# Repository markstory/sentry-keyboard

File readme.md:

# sentry-keyboard

A reverse engineered PCB for the keyboard that Sentry gave as holiday gift in 2024.

## Features

- Per key RGB LEDs
- Rotary encoder with switch
- USB host interface connection through picoblade connector.
- Programmable keymap with QMK

## Building the Firmware

The `firmware` directory of this repostiory contains only the files specific
to this keyboards firmware, and does not include all of QMK. To build firmware you
need to have a copy of QMK (lets assume it is at `~/code/qmk)`:

```bash
cp -R firmware/* ~/code/qmk/keyboards/sentry-keyboard
cd ~/code/qmk
qmk compile -kb sentry-keyboard -km default
```

This will compile a `.hex` file that you can flash onto your keyboard

```bash
qmk flash -kb sentry-keyboard
```

Brand new micro controller chips may have not have the bootloader initialized, 
and you'll need to erase the chip first:

```bash
dfu-programmer atmega32u4 erase
```

Once the chip has been erased you can flash the firmware on.

## License

Both the PCB design and firmware are provided under the MIT License

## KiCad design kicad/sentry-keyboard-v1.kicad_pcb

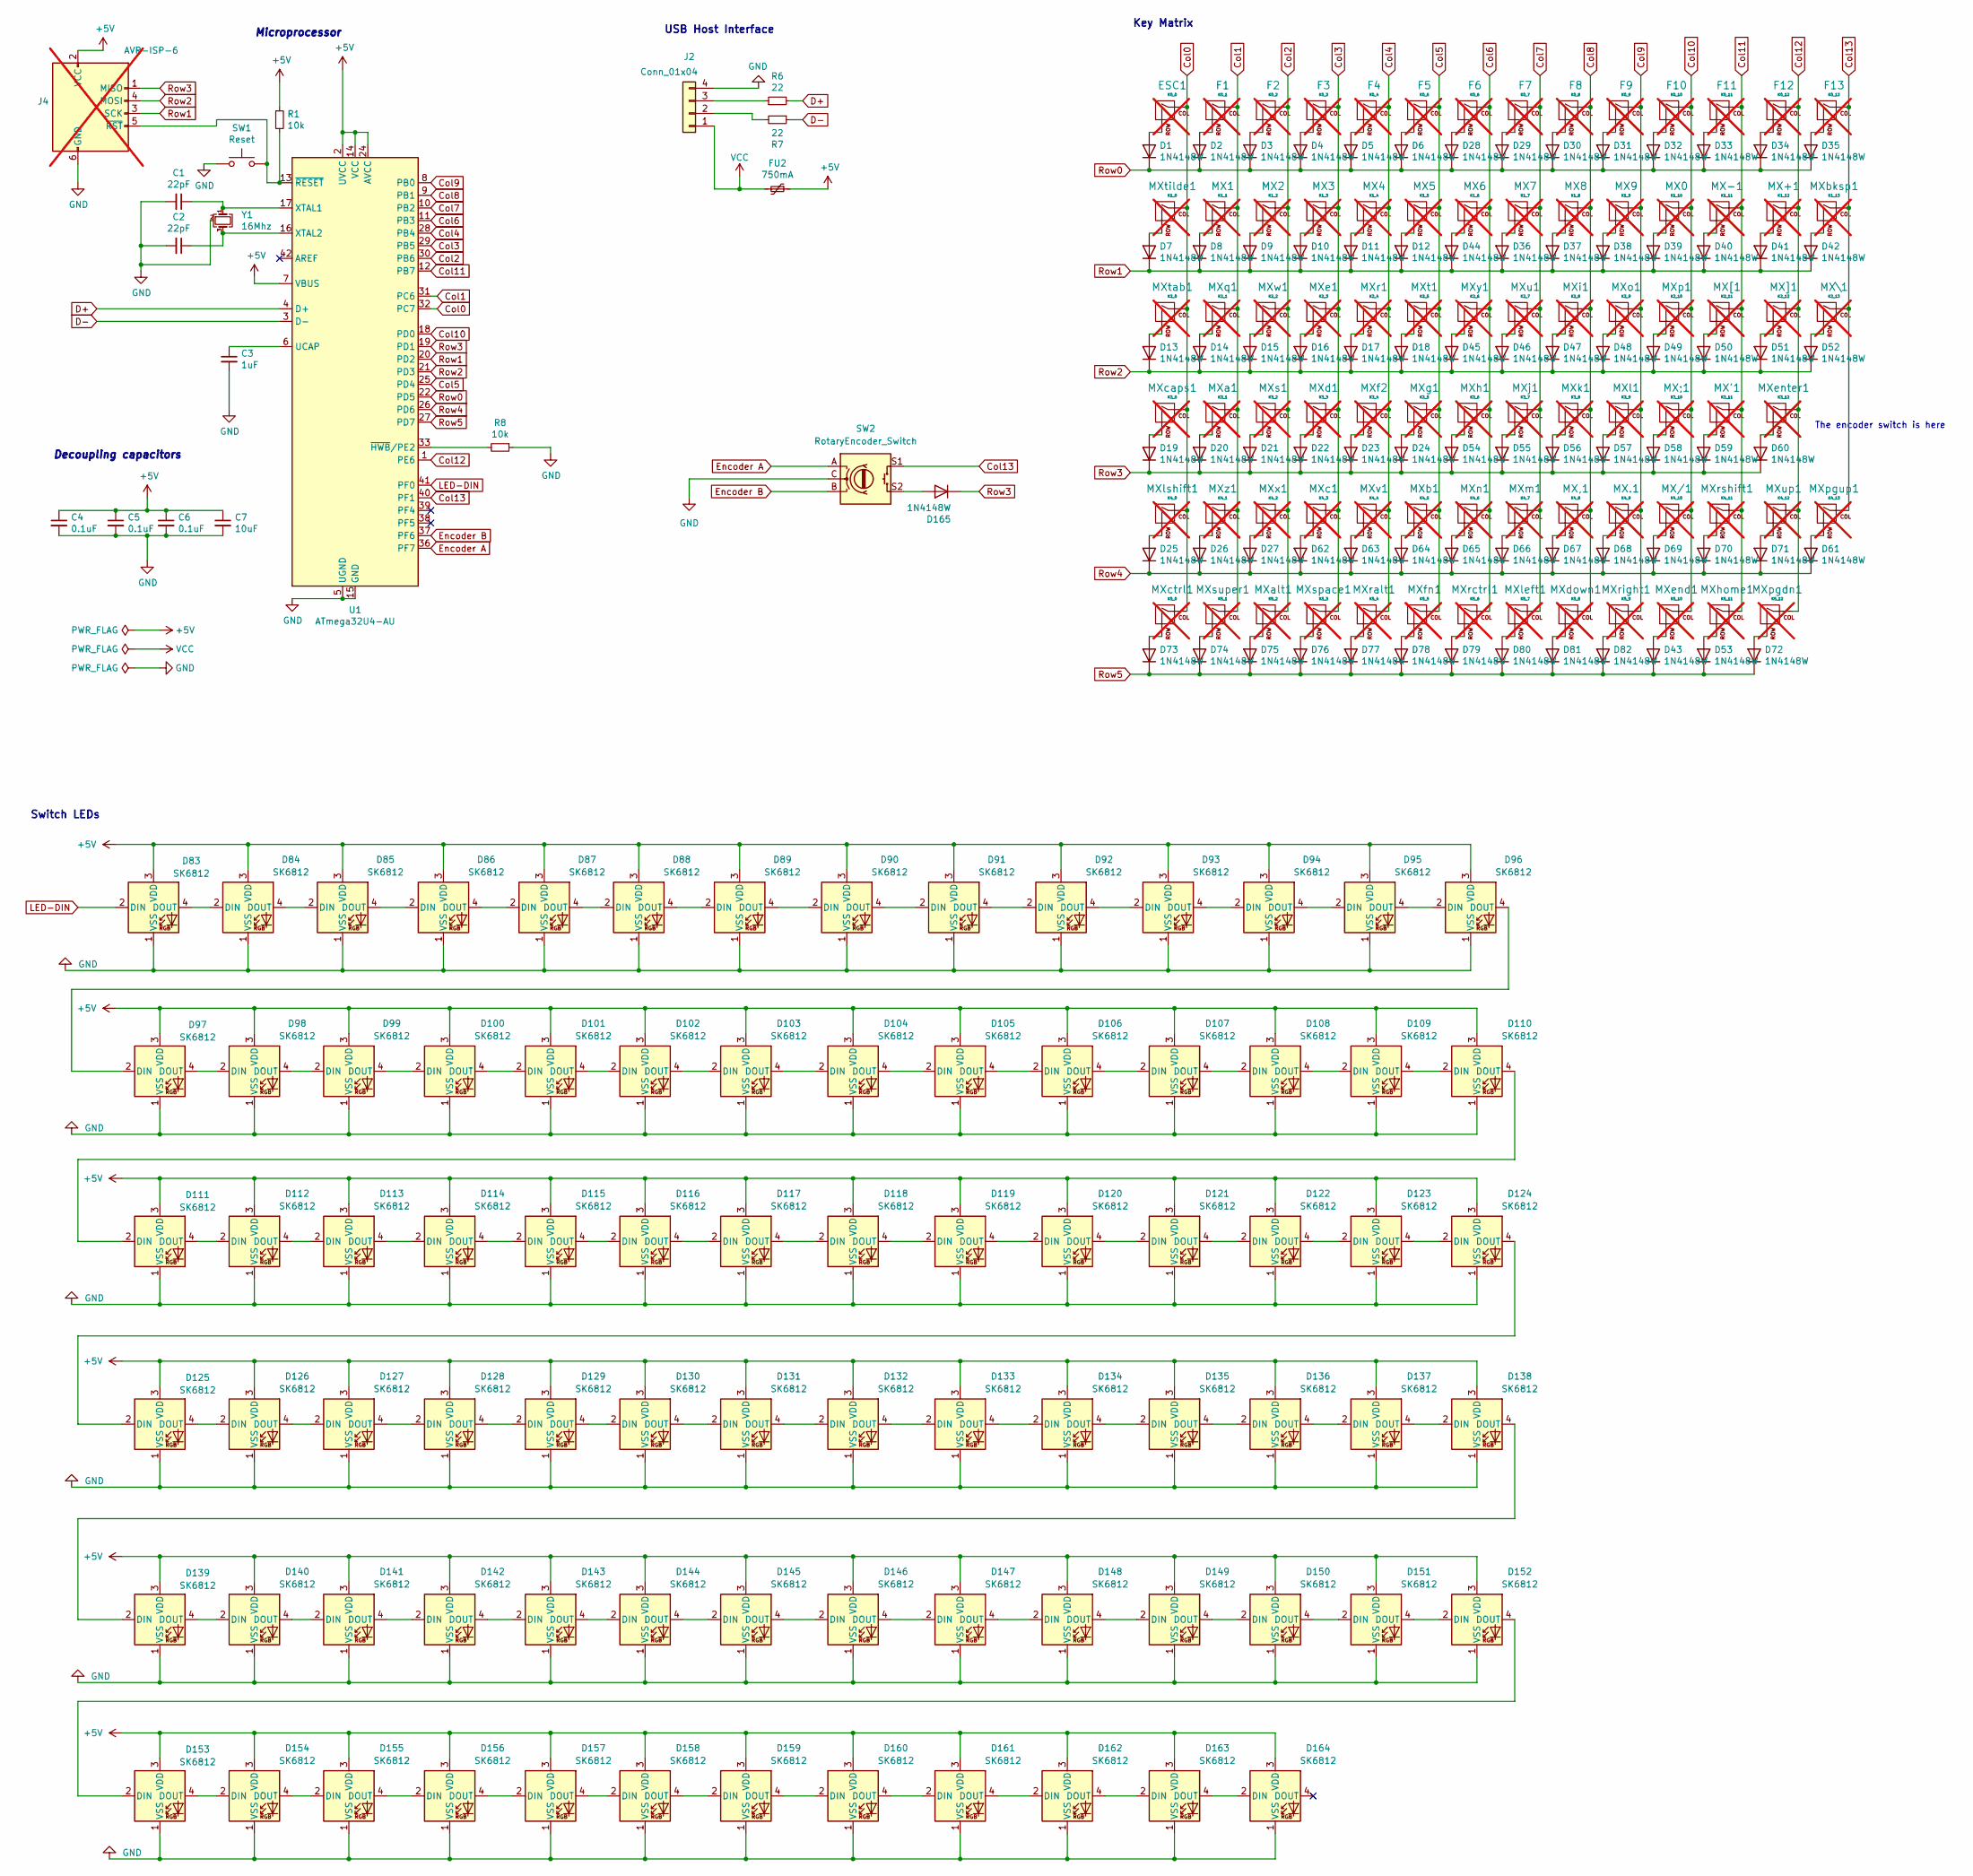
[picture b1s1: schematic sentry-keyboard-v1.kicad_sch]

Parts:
C1, C2: 22pF; C_0805_2012Metric; LCSC Part # C105623
C3: 1uF; C_0805_2012Metric; LCSC Part # C472813
C4, C5, C6: 0.1uF; C_0805_2012Metric; LCSC Part # C49678
C7: 10uF; C_0805_2012Metric; LCSC Part # C307520
D1, D2, D3, D4, D5, D6, D7, D8, D9, D10, D11, D12, D13, D14, D15, D16, D17, D18, D19, D20, D21, D22, D23, D24, D25, D26, D27, D28, D29, D30, D31, D32, D33, D34, D35, D36, D37, D38, D39, D40, D41, D42, D43, D44, D45, D46, D47, D48, D49, D50, D51, D52, D53, D54, D55, D56, D57, D58, D59, D60, D61, D62, D63, D64, D65, D66, D67, D68, D69, D70, D71, D72, D73, D74, D75, D76, D77, D78, D79, D80, D81, D82, D165: 1N4148W; D_SOD-123; LCSC Part # C7420318
D83, D84, D85, D86, D87, D88, D89, D90, D91, D92, D93, D94, D95, D96, D97, D98, D99, D100, D101, D102, D103, D104, D105, D106, D107, D108, D109, D110, D111, D112, D113, D114, D115, D116, D117, D118, D119, D120, D121, D122, D123, D124, D125, D126, D127, D128, D129, D130, D131, D132, D133, D134, D135, D136, D137, D138, D139, D140, D141, D142, D143, D144, D145, D146, D147, D148, D149, D150, D151, D152, D153, D154, D155, D156, D157, D158, D159, D160, D161, D162, D163, D164: SK6812; SK6812-MINI-E; LCSC Part # C5149201
ESC1: K0_0; MX-Hotswap-1U; not fitted
F1: K0_1; MX-Hotswap-1U; not fitted
F2: K0_2; MX-Hotswap-1U; not fitted
F3: K0_3; MX-Hotswap-1U; not fitted
F4: K0_4; MX-Hotswap-1U; not fitted
F5: K0_5; MX-Hotswap-1U; not fitted
F6: K0_6; MX-Hotswap-1U; not fitted
F7: K0_7; MX-Hotswap-1U; not fitted
F8: K0_8; MX-Hotswap-1U; not fitted
F9: K0_9; MX-Hotswap-1U; not fitted
F10: K0_10; MX-Hotswap-1U; not fitted
F11: K0_11; MX-Hotswap-1U; not fitted
F12: K0_12; MX-Hotswap-1U; not fitted
F13: K0_13; MX-Hotswap-1U; not fitted
FU2: 750mA; Fuse_1206_3216Metric_Pad1.42x1.75mm_HandSolder; LCSC Part # C46641018
J2: Conn_01x04; Molex_PicoBlade_53261-0471_1x04-1MP_P1.25mm_Horizontal; LCSC Part # C696092
J4: AVR-ISP-6; Reset_Pretty-Mask; not fitted
MX0: K1_10; MX-Hotswap-1U; not fitted
MX1: K1_1; MX-Hotswap-1U; not fitted
MX2: K1_2; MX-Hotswap-1U; not fitted
MX3: K1_3; MX-Hotswap-1U; not fitted
MX4: K1_4; MX-Hotswap-1U; not fitted
MX5: K1_5; MX-Hotswap-1U; not fitted
MX6: K1_6; MX-Hotswap-1U; not fitted
MX7: K1_7; MX-Hotswap-1U; not fitted
MX8: K1_8; MX-Hotswap-1U; not fitted
MX9: K1_9; MX-Hotswap-1U; not fitted
MX'1: K3_11; MX-Hotswap-1U; not fitted
MX+1: K1_12; MX-Hotswap-1U; not fitted
MX,1: K4_8; MX-Hotswap-1U; not fitted
MX-1: K1_11; MX-Hotswap-1U; not fitted
MX.1: K4_9; MX-Hotswap-1U; not fitted
MX/1: K4_10; MX-Hotswap-1U; not fitted
MX;1: K3_10; MX-Hotswap-1U; not fitted
MX[1: K2_11; MX-Hotswap-1U; not fitted
MX\1: K2_13; MX-Hotswap-1.5U; not fitted
MX]1: K2_12; MX-Hotswap-1U; not fitted
MXa1: K3_1; MX-Hotswap-1U; not fitted
MXalt1: K5_2; MX-Hotswap-1.25U; not fitted
MXb1: K4_5; MX-Hotswap-1U; not fitted
MXbksp1: K1_13; MX-Hotswap-2U; not fitted
MXc1: K4_3; MX-Hotswap-1U; not fitted
MXcaps1: K3_0; MX-Hotswap-1.75U; not fitted
MXctrl1: K5_0; MX-Hotswap-1.25U; not fitted
MXd1: K3_3; MX-Hotswap-1U; not fitted
MXdown1: K5_8; MX-Hotswap-1U; not fitted
MXe1: K2_3; MX-Hotswap-1U; not fitted
MXend1: K5_10; MX-Hotswap-1U; not fitted
MXenter1: K3_12; MX-Hotswap-2.25U-ReversedStabilizers; not fitted
MXf2: K3_4; MX-Hotswap-1U; not fitted
MXfn1: K5_5; MX-Hotswap-1U; not fitted
MXg1: K3_5; MX-Hotswap-1U; not fitted
MXh1: K3_6; MX-Hotswap-1U; not fitted
MXhome1: K5_11; MX-Hotswap-1U; not fitted
MXi1: K2_8; MX-Hotswap-1U; not fitted
MXj1: K3_7; MX-Hotswap-1U; not fitted
MXk1: K3_8; MX-Hotswap-1U; not fitted
MXl1: K3_9; MX-Hotswap-1U; not fitted
MXleft1: K5_7; MX-Hotswap-1U; not fitted
MXlshift1: K4_0; MX-Hotswap-2.25U; not fitted
MXm1: K4_7; MX-Hotswap-1U; not fitted
MXn1: K4_6; MX-Hotswap-1U; not fitted
MXo1: K2_9; MX-Hotswap-1U; not fitted
MXp1: K2_10; MX-Hotswap-1U; not fitted
MXpgdn1: K5_12; MX-Hotswap-1U; not fitted
MXpgup1: K4_13; MX-Hotswap-1U; not fitted
MXq1: K2_1; MX-Hotswap-1U; not fitted
MXr1: K2_4; MX-Hotswap-1U; not fitted
MXralt1: K5_4; MX-Hotswap-1U; not fitted
MXrctrl1: K5_6; MX-Hotswap-1U; not fitted
MXright1: K5_9; MX-Hotswap-1U; not fitted
MXrshift1: K4_11; MX-Hotswap-1.75U; not fitted
MXs1: K3_2; MX-Hotswap-1U; not fitted
MXspace1: K5_3; MX-Hotswap-6.25U-ReversedStabilizers; not fitted
MXsuper1: K5_1; MX-Hotswap-1.25U; not fitted
MXt1: K2_5; MX-Hotswap-1U; not fitted
MXtab1: K2_0; MX-Hotswap-1.5U; not fitted
MXtilde1: K1_0; MX-Hotswap-1U; not fitted
MXu1: K2_7; MX-Hotswap-1U; not fitted
MXup1: K4_12; MX-Hotswap-1U; not fitted
MXv1: K4_4; MX-Hotswap-1U; not fitted
MXw1: K2_2; MX-Hotswap-1U; not fitted
MXx1: K4_2; MX-Hotswap-1U; not fitted
MXy1: K2_6; MX-Hotswap-1U; not fitted
MXz1: K4_1; MX-Hotswap-1U; not fitted
R1, R8: 10k; R_0805_2012Metric; LCSC Part # C180849
R6, R7: 22; R_0805_2012Metric; LCSC Part # C413152
SW1: Reset; SW_SPST_TL3342; LCSC Part # C720467
SW2: RotaryEncoder_Switch; RotaryEncoder_EC11; LCSC Part # C470748
U1: ATmega32U4-AU; TQFP-44_10x10mm_P0.8mm; LCSC Part # C44854
Y1: 16Mhz; Crystal_SMD_3225-4Pin_3.2x2.5mm; LCSC Part # C258944

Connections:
+5V: C4.1, C5.1, C6.1, C7.1, D83.3 (VDD), D84.3 (VDD), D85.3 (VDD), D86.3 (VDD), D87.3 (VDD), D88.3 (VDD), D89.3 (VDD), D90.3 (VDD), D91.3 (VDD), D92.3 (VDD), D93.3 (VDD), D94.3 (VDD), D95.3 (VDD), D96.3 (VDD), D97.3 (VDD), D98.3 (VDD), D99.3 (VDD), D100.3 (VDD), D101.3 (VDD), D102.3 (VDD), D103.3 (VDD), D104.3 (VDD), D105.3 (VDD), D106.3 (VDD), D107.3 (VDD), D108.3 (VDD), D109.3 (VDD), D110.3 (VDD), D111.3 (VDD), D112.3 (VDD), D113.3 (VDD), D114.3 (VDD), D115.3 (VDD), D116.3 (VDD), D117.3 (VDD), D118.3 (VDD), D119.3 (VDD), D120.3 (VDD), D121.3 (VDD), D122.3 (VDD), D123.3 (VDD), D124.3 (VDD), D125.3 (VDD), D126.3 (VDD), D127.3 (VDD), D128.3 (VDD), D129.3 (VDD), D130.3 (VDD), D131.3 (VDD), D132.3 (VDD), D133.3 (VDD), D134.3 (VDD), D135.3 (VDD), D136.3 (VDD), D137.3 (VDD), D138.3 (VDD), D139.3 (VDD), D140.3 (VDD), D141.3 (VDD), D142.3 (VDD), D143.3 (VDD), D144.3 (VDD), D145.3 (VDD), D146.3 (VDD), D147.3 (VDD), D148.3 (VDD), D149.3 (VDD), D150.3 (VDD), D151.3 (VDD), D152.3 (VDD), D153.3 (VDD), D154.3 (VDD), D155.3 (VDD), D156.3 (VDD), D157.3 (VDD), D158.3 (VDD), D159.3 (VDD), D160.3 (VDD), D161.3 (VDD), D162.3 (VDD), D163.3 (VDD), D164.3 (VDD), FU2.1, J4.2 (VCC), R1.1, U1.2 (UVCC), U1.7 (VBUS), U1.14 (VCC), U1.24 (AVCC), U1.34 (VCC), U1.44 (AVCC)
Col0: ESC1.1 (COL), MXcaps1.1 (COL), MXctrl1.1 (COL), MXlshift1.1 (COL), MXtab1.1 (COL), MXtilde1.1 (COL), U1.32 (PC7)
Col1: F1.1 (COL), MX1.1 (COL), MXa1.1 (COL), MXq1.1 (COL), MXsuper1.1 (COL), MXz1.1 (COL), U1.31 (PC6)
Col2: F2.1 (COL), MX2.1 (COL), MXalt1.1 (COL), MXs1.1 (COL), MXw1.1 (COL), MXx1.1 (COL), U1.30 (PB6)
Col3: F3.1 (COL), MX3.1 (COL), MXc1.1 (COL), MXd1.1 (COL), MXe1.1 (COL), MXspace1.1 (COL), U1.29 (PB5)
Col4: F4.1 (COL), MX4.1 (COL), MXf2.1 (COL), MXr1.1 (COL), MXralt1.1 (COL), MXv1.1 (COL), U1.28 (PB4)
Col5: F5.1 (COL), MX5.1 (COL), MXb1.1 (COL), MXfn1.1 (COL), MXg1.1 (COL), MXt1.1 (COL), U1.25 (PD4)
Col6: F6.1 (COL), MX6.1 (COL), MXh1.1 (COL), MXn1.1 (COL), MXrctrl1.1 (COL), MXy1.1 (COL), U1.11 (PB3)
Col7: F7.1 (COL), MX7.1 (COL), MXj1.1 (COL), MXleft1.1 (COL), MXm1.1 (COL), MXu1.1 (COL), U1.10 (PB2)
Col8: F8.1 (COL), MX8.1 (COL), MX,1.1 (COL), MXdown1.1 (COL), MXi1.1 (COL), MXk1.1 (COL), U1.9 (PB1)
Col9: F9.1 (COL), MX9.1 (COL), MX.1.1 (COL), MXl1.1 (COL), MXo1.1 (COL), MXright1.1 (COL), U1.8 (PB0)
Col10: F10.1 (COL), MX0.1 (COL), MX/1.1 (COL), MX;1.1 (COL), MXend1.1 (COL), MXp1.1 (COL), U1.18 (PD0)
Col11: F11.1 (COL), MX'1.1 (COL), MX-1.1 (COL), MX[1.1 (COL), MXhome1.1 (COL), MXrshift1.1 (COL), U1.12 (PB7)
Col12: F12.1 (COL), MX+1.1 (COL), MX]1.1 (COL), MXenter1.1 (COL), MXpgdn1.1 (COL), MXup1.1 (COL), U1.1 (PE6)
Col13: F13.1 (COL), MX\1.1 (COL), MXbksp1.1 (COL), MXpgup1.1 (COL), SW2.S1, U1.40 (PF1)
D+: R6.2, U1.4 (D+)
D-: R7.1, U1.3 (D-)
Encoder A: SW2.A, U1.36 (PF7)
Encoder B: SW2.B, U1.37 (PF6)
GND: C1.2, C2.2, C3.2, C4.2, C5.2, C6.2, C7.2, D83.1 (VSS), D84.1 (VSS), D85.1 (VSS), D86.1 (VSS), D87.1 (VSS), D88.1 (VSS), D89.1 (VSS), D90.1 (VSS), D91.1 (VSS), D92.1 (VSS), D93.1 (VSS), D94.1 (VSS), D95.1 (VSS), D96.1 (VSS), D97.1 (VSS), D98.1 (VSS), D99.1 (VSS), D100.1 (VSS), D101.1 (VSS), D102.1 (VSS), D103.1 (VSS), D104.1 (VSS), D105.1 (VSS), D106.1 (VSS), D107.1 (VSS), D108.1 (VSS), D109.1 (VSS), D110.1 (VSS), D111.1 (VSS), D112.1 (VSS), D113.1 (VSS), D114.1 (VSS), D115.1 (VSS), D116.1 (VSS), D117.1 (VSS), D118.1 (VSS), D119.1 (VSS), D120.1 (VSS), D121.1 (VSS), D122.1 (VSS), D123.1 (VSS), D124.1 (VSS), D125.1 (VSS), D126.1 (VSS), D127.1 (VSS), D128.1 (VSS), D129.1 (VSS), D130.1 (VSS), D131.1 (VSS), D132.1 (VSS), D133.1 (VSS), D134.1 (VSS), D135.1 (VSS), D136.1 (VSS), D137.1 (VSS), D138.1 (VSS), D139.1 (VSS), D140.1 (VSS), D141.1 (VSS), D142.1 (VSS), D143.1 (VSS), D144.1 (VSS), D145.1 (VSS), D146.1 (VSS), D147.1 (VSS), D148.1 (VSS), D149.1 (VSS), D150.1 (VSS), D151.1 (VSS), D152.1 (VSS), D153.1 (VSS), D154.1 (VSS), D155.1 (VSS), D156.1 (VSS), D157.1 (VSS), D158.1 (VSS), D159.1 (VSS), D160.1 (VSS), D161.1 (VSS), D162.1 (VSS), D163.1 (VSS), D164.1 (VSS), J2.4, J4.6 (GND), R8.1, SW1.1, SW2.C, U1.5 (UGND), U1.15 (GND), U1.23 (GND), U1.35 (GND), U1.43 (GND), Y1.2 (G), Y1.4 (G)
LED-DIN: D83.2 (DIN), U1.41 (PF0)
unnamed: D1.2 (A), ESC1.2 (ROW)
unnamed: D2.2 (A), F1.2 (ROW)
unnamed: D3.2 (A), F2.2 (ROW)
unnamed: D4.2 (A), F3.2 (ROW)
unnamed: D5.2 (A), F4.2 (ROW)
unnamed: D6.2 (A), F5.2 (ROW)
unnamed: D7.2 (A), MXtilde1.2 (ROW)
unnamed: D8.2 (A), MX1.2 (ROW)
unnamed: D9.2 (A), MX2.2 (ROW)
unnamed: D10.2 (A), MX3.2 (ROW)
unnamed: D11.2 (A), MX4.2 (ROW)
unnamed: D12.2 (A), MX5.2 (ROW)
unnamed: D13.2 (A), MXtab1.2 (ROW)
unnamed: D14.2 (A), MXq1.2 (ROW)
unnamed: D15.2 (A), MXw1.2 (ROW)
unnamed: D16.2 (A), MXe1.2 (ROW)
unnamed: D17.2 (A), MXr1.2 (ROW)
unnamed: D18.2 (A), MXt1.2 (ROW)
unnamed: D19.2 (A), MXcaps1.2 (ROW)
unnamed: D20.2 (A), MXa1.2 (ROW)
unnamed: D21.2 (A), MXs1.2 (ROW)
unnamed: D22.2 (A), MXd1.2 (ROW)
unnamed: D23.2 (A), MXf2.2 (ROW)
unnamed: D24.2 (A), MXg1.2 (ROW)
unnamed: D25.2 (A), MXlshift1.2 (ROW)
unnamed: D26.2 (A), MXz1.2 (ROW)
unnamed: D27.2 (A), MXx1.2 (ROW)
unnamed: D28.2 (A), F6.2 (ROW)
unnamed: D29.2 (A), F7.2 (ROW)
unnamed: D30.2 (A), F8.2 (ROW)
unnamed: D31.2 (A), F9.2 (ROW)
unnamed: D32.2 (A), F10.2 (ROW)
unnamed: D33.2 (A), F11.2 (ROW)
unnamed: D34.2 (A), F12.2 (ROW)
unnamed: D35.2 (A), F13.2 (ROW)
unnamed: D36.2 (A), MX7.2 (ROW)
unnamed: D37.2 (A), MX8.2 (ROW)
unnamed: D38.2 (A), MX9.2 (ROW)
unnamed: D39.2 (A), MX0.2 (ROW)
unnamed: D40.2 (A), MX-1.2 (ROW)
unnamed: D41.2 (A), MX+1.2 (ROW)
unnamed: D42.2 (A), MXbksp1.2 (ROW)
unnamed: D43.2 (A), MXend1.2 (ROW)
unnamed: D44.2 (A), MX6.2 (ROW)
unnamed: D45.2 (A), MXy1.2 (ROW)
unnamed: D46.2 (A), MXu1.2 (ROW)
unnamed: D47.2 (A), MXi1.2 (ROW)
unnamed: D48.2 (A), MXo1.2 (ROW)
unnamed: D49.2 (A), MXp1.2 (ROW)
unnamed: D50.2 (A), MX[1.2 (ROW)
unnamed: D51.2 (A), MX]1.2 (ROW)
unnamed: D52.2 (A), MX\1.2 (ROW)
unnamed: D53.2 (A), MXhome1.2 (ROW)
unnamed: D54.2 (A), MXh1.2 (ROW)
unnamed: D55.2 (A), MXj1.2 (ROW)
unnamed: D56.2 (A), MXk1.2 (ROW)
unnamed: D57.2 (A), MXl1.2 (ROW)
unnamed: D58.2 (A), MX;1.2 (ROW)
unnamed: D59.2 (A), MX'1.2 (ROW)
unnamed: D60.2 (A), MXenter1.2 (ROW)
unnamed: D61.2 (A), MXpgup1.2 (ROW)
unnamed: D62.2 (A), MXc1.2 (ROW)
unnamed: D63.2 (A), MXv1.2 (ROW)
unnamed: D64.2 (A), MXb1.2 (ROW)
unnamed: D65.2 (A), MXn1.2 (ROW)
unnamed: D66.2 (A), MXm1.2 (ROW)
unnamed: D67.2 (A), MX,1.2 (ROW)
unnamed: D68.2 (A), MX.1.2 (ROW)
unnamed: D69.2 (A), MX/1.2 (ROW)
unnamed: D70.2 (A), MXrshift1.2 (ROW)
unnamed: D71.2 (A), MXup1.2 (ROW)
unnamed: D72.2 (A), MXpgdn1.2 (ROW)
unnamed: D73.2 (A), MXctrl1.2 (ROW)
unnamed: D74.2 (A), MXsuper1.2 (ROW)
unnamed: D75.2 (A), MXalt1.2 (ROW)
unnamed: D76.2 (A), MXspace1.2 (ROW)
unnamed: D77.2 (A), MXralt1.2 (ROW)
unnamed: D78.2 (A), MXfn1.2 (ROW)
unnamed: D79.2 (A), MXrctrl1.2 (ROW)
unnamed: D80.2 (A), MXleft1.2 (ROW)
unnamed: D81.2 (A), MXdown1.2 (ROW)
unnamed: D82.2 (A), MXright1.2 (ROW)
unnamed: D83.4 (DOUT), D84.2 (DIN)
unnamed: D84.4 (DOUT), D85.2 (DIN)
unnamed: D85.4 (DOUT), D86.2 (DIN)
unnamed: D86.4 (DOUT), D87.2 (DIN)
unnamed: D87.4 (DOUT), D88.2 (DIN)
unnamed: D88.4 (DOUT), D89.2 (DIN)
unnamed: D89.4 (DOUT), D90.2 (DIN)
unnamed: D90.4 (DOUT), D91.2 (DIN)
unnamed: D91.4 (DOUT), D92.2 (DIN)
unnamed: D92.4 (DOUT), D93.2 (DIN)
unnamed: D93.4 (DOUT), D94.2 (DIN)
unnamed: D94.4 (DOUT), D95.2 (DIN)
unnamed: D95.4 (DOUT), D96.2 (DIN)
unnamed: D96.4 (DOUT), D97.2 (DIN)
unnamed: D97.4 (DOUT), D98.2 (DIN)
unnamed: D98.4 (DOUT), D99.2 (DIN)
unnamed: D99.4 (DOUT), D100.2 (DIN)
unnamed: D100.4 (DOUT), D101.2 (DIN)
unnamed: D101.4 (DOUT), D102.2 (DIN)
unnamed: D102.4 (DOUT), D103.2 (DIN)
unnamed: D103.4 (DOUT), D104.2 (DIN)
unnamed: D104.4 (DOUT), D105.2 (DIN)
unnamed: D105.4 (DOUT), D106.2 (DIN)
unnamed: D106.4 (DOUT), D107.2 (DIN)
unnamed: D107.4 (DOUT), D108.2 (DIN)
unnamed: D108.4 (DOUT), D109.2 (DIN)
unnamed: D109.4 (DOUT), D110.2 (DIN)
unnamed: D110.4 (DOUT), D111.2 (DIN)
unnamed: D111.4 (DOUT), D112.2 (DIN)
unnamed: D112.4 (DOUT), D113.2 (DIN)
unnamed: D113.4 (DOUT), D114.2 (DIN)
unnamed: D114.4 (DOUT), D115.2 (DIN)
unnamed: D115.4 (DOUT), D116.2 (DIN)
unnamed: D116.4 (DOUT), D117.2 (DIN)
unnamed: D117.4 (DOUT), D118.2 (DIN)
unnamed: D118.4 (DOUT), D119.2 (DIN)
unnamed: D119.4 (DOUT), D120.2 (DIN)
unnamed: D120.4 (DOUT), D121.2 (DIN)
unnamed: D121.4 (DOUT), D122.2 (DIN)
unnamed: D122.4 (DOUT), D123.2 (DIN)
unnamed: D123.4 (DOUT), D124.2 (DIN)
unnamed: D124.4 (DOUT), D125.2 (DIN)
unnamed: D125.4 (DOUT), D126.2 (DIN)
unnamed: D126.4 (DOUT), D127.2 (DIN)
unnamed: D127.4 (DOUT), D128.2 (DIN)
unnamed: D128.4 (DOUT), D129.2 (DIN)
unnamed: D129.4 (DOUT), D130.2 (DIN)
unnamed: D130.4 (DOUT), D131.2 (DIN)
unnamed: D131.4 (DOUT), D132.2 (DIN)
unnamed: D132.4 (DOUT), D133.2 (DIN)
unnamed: D133.4 (DOUT), D134.2 (DIN)
unnamed: D134.4 (DOUT), D135.2 (DIN)
unnamed: D135.4 (DOUT), D136.2 (DIN)
unnamed: D136.4 (DOUT), D137.2 (DIN)
unnamed: D137.4 (DOUT), D138.2 (DIN)
unnamed: D138.4 (DOUT), D139.2 (DIN)
unnamed: D139.4 (DOUT), D140.2 (DIN)
unnamed: D140.4 (DOUT), D141.2 (DIN)
unnamed: D141.4 (DOUT), D142.2 (DIN)
unnamed: D142.4 (DOUT), D143.2 (DIN)
unnamed: D143.4 (DOUT), D144.2 (DIN)
unnamed: D144.4 (DOUT), D145.2 (DIN)
unnamed: D145.4 (DOUT), D146.2 (DIN)
unnamed: D146.4 (DOUT), D147.2 (DIN)
unnamed: D147.4 (DOUT), D148.2 (DIN)
unnamed: D148.4 (DOUT), D149.2 (DIN)
unnamed: D149.4 (DOUT), D150.2 (DIN)
unnamed: D150.4 (DOUT), D151.2 (DIN)
unnamed: D151.4 (DOUT), D152.2 (DIN)
unnamed: D152.4 (DOUT), D153.2 (DIN)
unnamed: D153.4 (DOUT), D154.2 (DIN)
unnamed: D154.4 (DOUT), D155.2 (DIN)
unnamed: D155.4 (DOUT), D156.2 (DIN)
unnamed: D156.4 (DOUT), D157.2 (DIN)
unnamed: D157.4 (DOUT), D158.2 (DIN)
unnamed: D158.4 (DOUT), D159.2 (DIN)
unnamed: D159.4 (DOUT), D160.2 (DIN)
unnamed: D160.4 (DOUT), D161.2 (DIN)
unnamed: D161.4 (DOUT), D162.2 (DIN)
unnamed: D162.4 (DOUT), D163.2 (DIN)
unnamed: D163.4 (DOUT), D164.2 (DIN)
unnamed: D165.2 (A), SW2.S2
unnamed: J2.2, R7.2
unnamed: J2.3, R6.1
unnamed: J4.5 (~RST), R1.2, SW1.2, U1.13 (~RESET)
unnamed: C3.1, U1.6 (UCAP)
unnamed: C1.1, U1.17 (XTAL1), Y1.1
unnamed: C2.1, U1.16 (XTAL2), Y1.3
unnamed: R8.2, U1.33 (~HWB/PE2)
Row0: D1.1 (K), D2.1 (K), D3.1 (K), D4.1 (K), D5.1 (K), D6.1 (K), D28.1 (K), D29.1 (K), D30.1 (K), D31.1 (K), D32.1 (K), D33.1 (K), D34.1 (K), D35.1 (K), U1.22 (PD5)
Row1: D7.1 (K), D8.1 (K), D9.1 (K), D10.1 (K), D11.1 (K), D12.1 (K), D36.1 (K), D37.1 (K), D38.1 (K), D39.1 (K), D40.1 (K), D41.1 (K), D42.1 (K), D44.1 (K), J4.3 (SCK), U1.20 (PD2)
Row2: D13.1 (K), D14.1 (K), D15.1 (K), D16.1 (K), D17.1 (K), D18.1 (K), D45.1 (K), D46.1 (K), D47.1 (K), D48.1 (K), D49.1 (K), D50.1 (K), D51.1 (K), D52.1 (K), J4.4 (MOSI), U1.21 (PD3)
Row3: D19.1 (K), D20.1 (K), D21.1 (K), D22.1 (K), D23.1 (K), D24.1 (K), D54.1 (K), D55.1 (K), D56.1 (K), D57.1 (K), D58.1 (K), D59.1 (K), D60.1 (K), D165.1 (K), J4.1 (MISO), U1.19 (PD1)
Row4: D25.1 (K), D26.1 (K), D27.1 (K), D61.1 (K), D62.1 (K), D63.1 (K), D64.1 (K), D65.1 (K), D66.1 (K), D67.1 (K), D68.1 (K), D69.1 (K), D70.1 (K), D71.1 (K), U1.26 (PD6)
Row5: D43.1 (K), D53.1 (K), D72.1 (K), D73.1 (K), D74.1 (K), D75.1 (K), D76.1 (K), D77.1 (K), D78.1 (K), D79.1 (K), D80.1 (K), D81.1 (K), D82.1 (K), U1.27 (PD7)
VCC: FU2.2, J2.1

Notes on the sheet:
Switch LEDs
USB Host Interface
Microprocessor
Decoupling capacitors
The encoder switch is here
Key Matrix

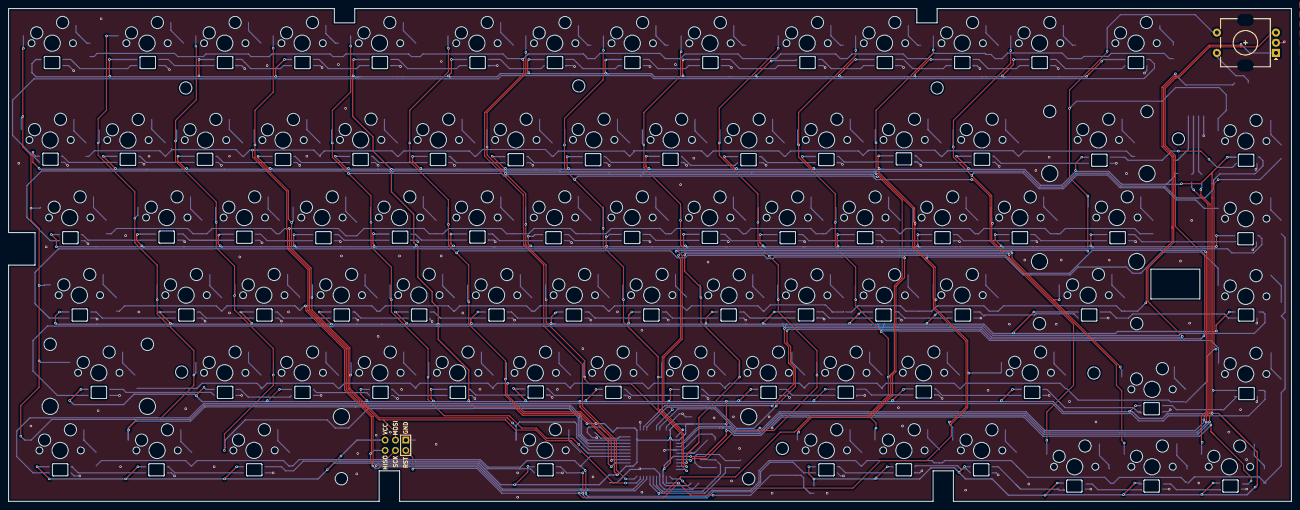
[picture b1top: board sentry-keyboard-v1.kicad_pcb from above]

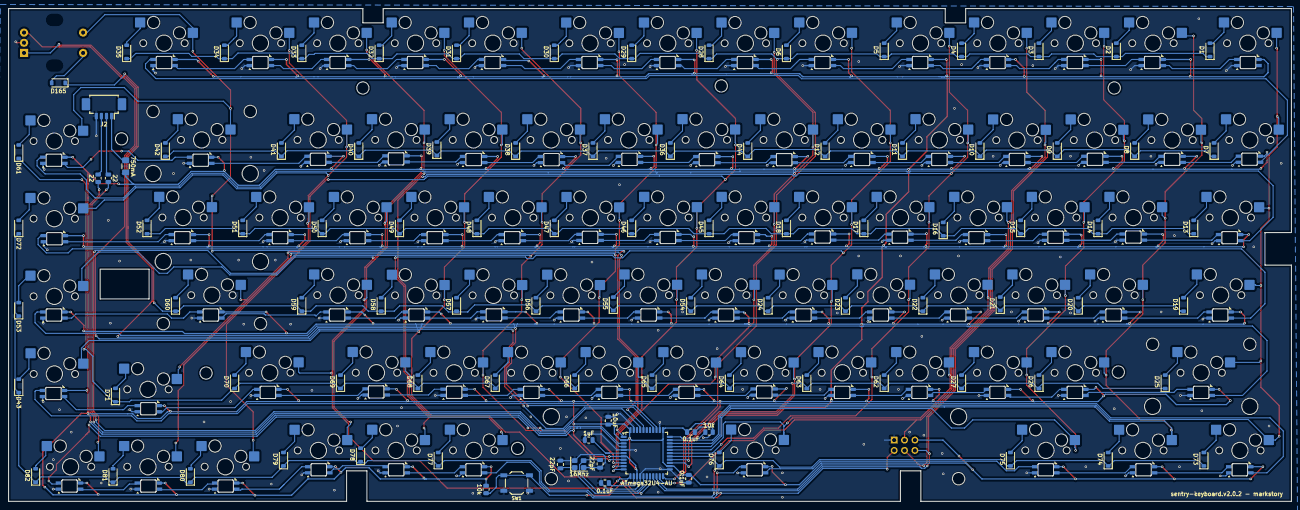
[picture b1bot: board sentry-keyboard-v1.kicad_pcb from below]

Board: 2 copper layers, 315.0 x 121.0 mm, 265 parts (263 on the bottom side), 199 nets.

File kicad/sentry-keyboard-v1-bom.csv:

"Id";"Designator";"Footprint";"Quantity";"Designation";"Supplier and ref";
1;"J4";"Reset_Pretty-Mask";1;"AVR-ISP-6";;;
2;"SW2";"RotaryEncoder_EC11";1;"RotaryEncoder_Switch";;;
3;"D62,D77,D46,D66,D32,D27,D79,D43,D65,D49,D42,D165,D64,D8,D61,D73,D81,D41,D69,D50,D1,D52,D34,D37,D14,D58,D76,D21,D45,D51,D31,D68,D2,D25,D10,D67,D30,D35,D23,D38,D6,D47,D9,D15,D57,D53,D59,D72,D11,D13,D12,D54,D80,D60,D28,D74,D16,D56,D17,D22,D33,D5,D24,D26,D48,D4,D44,D63,D3,D70,D40,D36,D78,D39,D20,D82,D7,D71,D18,D55,D19,D29,D75";"D_SOD-123";83;"1N4148W";;;
4;"D160,D126,D150,D96,D119,D147,D87,D109,D152,D105,D146,D110,D133,D85,D159,D88,D162,D90,D144,D134,D138,D84,D129,D132,D153,D83,D135,D145,D89,D141,D118,D108,D91,D104,D113,D137,D155,D98,D128,D157,D94,D151,D140,D107,D103,D149,D131,D114,D102,D148,D122,D116,D100,D115,D95,D86,D130,D111,D156,D120,D123,D93,D158,D117,D136,D106,D112,D161,D92,D101,D125,D164,D121,D139,D99,D124,D154,D143,D127,D142,D163,D97";"SK6812-MINI-E";82;"SK6812";;;
5;"C4,C6,C5";"C_0805_2012Metric";3;"0.1uF";;;
6;"C7";"C_0805_2012Metric";1;"10uF";;;
7;"MXr1";"MX-Hotswap-1U";1;"K2_4";;;
8;"MXx1";"MX-Hotswap-1U";1;"K4_2";;;
9;"MXlshift1";"MX-Hotswap-2.25U";1;"K4_0";;;
10;"MXend1";"MX-Hotswap-1U";1;"K5_10";;;
11;"MXspace1";"MX-Hotswap-6.25U-ReversedStabilizers";1;"K5_3";;;
12;"MXrshift1";"MX-Hotswap-1.75U";1;"K4_11";;;
13;"MX;1";"MX-Hotswap-1U";1;"K3_10";;;
14;"MX.1";"MX-Hotswap-1U";1;"K4_9";;;
15;"MXh1";"MX-Hotswap-1U";1;"K3_6";;;
16;"R1,R8";"R_0805_2012Metric";2;"10k";;;
17;"C1,C2";"C_0805_2012Metric";2;"22pF";;;
18;"C3";"C_0805_2012Metric";1;"1uF";;;
19;"MXq1";"MX-Hotswap-1U";1;"K2_1";;;
20;"MX1";"MX-Hotswap-1U";1;"K1_1";;;
21;"MX\1";"MX-Hotswap-1.5U";1;"K2_13";;;
22;"MXbksp1";"MX-Hotswap-2U";1;"K1_13";;;
23;"MXa1";"MX-Hotswap-1U";1;"K3_1";;;
24;"MXb1";"MX-Hotswap-1U";1;"K4_5";;;
25;"MXj1";"MX-Hotswap-1U";1;"K3_7";;;
26;"SW1";"SW_SPST_TL3342";1;"Reset";;;
27;"MX0";"MX-Hotswap-1U";1;"K1_10";;;
28;"F9";"MX-Hotswap-1U";1;"K0_9";;;
29;"MXhome1";"MX-Hotswap-1U";1;"K5_11";;;
30;"MXv1";"MX-Hotswap-1U";1;"K4_4";;;
31;"MXalt1";"MX-Hotswap-1.25U";1;"K5_2";;;
32;"MX4";"MX-Hotswap-1U";1;"K1_4";;;
33;"MXn1";"MX-Hotswap-1U";1;"K4_6";;;
34;"MX/1";"MX-Hotswap-1U";1;"K4_10";;;
35;"MXright1";"MX-Hotswap-1U";1;"K5_9";;;
36;"MXw1";"MX-Hotswap-1U";1;"K2_2";;;
37;"MXtilde1";"MX-Hotswap-1U";1;"K1_0";;;
38;"MXleft1";"MX-Hotswap-1U";1;"K5_7";;;
39;"U1";"TQFP-44_10x10mm_P0.8mm";1;"ATmega32U4-AU";;;
40;"F5";"MX-Hotswap-1U";1;"K0_5";;;
41;"MX5";"MX-Hotswap-1U";1;"K1_5";;;
42;"MXralt1";"MX-Hotswap-1U";1;"K5_4";;;
43;"MXup1";"MX-Hotswap-1U";1;"K4_12";;;
44;"MX3";"MX-Hotswap-1U";1;"K1_3";;;
45;"MXu1";"MX-Hotswap-1U";1;"K2_7";;;
46;"MXd1";"MX-Hotswap-1U";1;"K3_3";;;
47;"MXk1";"MX-Hotswap-1U";1;"K3_8";;;
48;"F7";"MX-Hotswap-1U";1;"K0_7";;;
49;"MXi1";"MX-Hotswap-1U";1;"K2_8";;;
50;"MXpgdn1";"MX-Hotswap-1U";1;"K5_12";;;
51;"F2";"MX-Hotswap-1U";1;"K0_2";;;
52;"MXpgup1";"MX-Hotswap-1U";1;"K4_13";;;
53;"F3";"MX-Hotswap-1U";1;"K0_3";;;
54;"R7,R6";"R_0805_2012Metric";2;"22";;;
55;"MXg1";"MX-Hotswap-1U";1;"K3_5";;;
56;"MX2";"MX-Hotswap-1U";1;"K1_2";;;
57;"MXz1";"MX-Hotswap-1U";1;"K4_1";;;
58;"MXt1";"MX-Hotswap-1U";1;"K2_5";;;
59;"J2";"Molex_PicoBlade_53261-0471_1x04-1MP_P1.25mm_Horizontal";1;"Conn_01x04";;;
60;"MX'1";"MX-Hotswap-1U";1;"K3_11";;;
61;"F4";"MX-Hotswap-1U";1;"K0_4";;;
62;"F10";"MX-Hotswap-1U";1;"K0_10";;;
63;"MXrctrl1";"MX-Hotswap-1U";1;"K5_6";;;
64;"FU2";"Fuse_1206_3216Metric_Pad1.42x1.75mm_HandSolder";1;"500mA";;;
65;"MXs1";"MX-Hotswap-1U";1;"K3_2";;;
66;"F12";"MX-Hotswap-1U";1;"K0_12";;;
67;"MX-1";"MX-Hotswap-1U";1;"K1_11";;;
68;"MX[1";"MX-Hotswap-1U";1;"K2_11";;;
69;"F6";"MX-Hotswap-1U";1;"K0_6";;;
70;"MXdown1";"MX-Hotswap-1U";1;"K5_8";;;
71;"MXl1";"MX-Hotswap-1U";1;"K3_9";;;
72;"F8";"MX-Hotswap-1U";1;"K0_8";;;
73;"MXfn1";"MX-Hotswap-1U";1;"K5_5";;;
74;"MX,1";"MX-Hotswap-1U";1;"K4_8";;;
75;"F11";"MX-Hotswap-1U";1;"K0_11";;;
76;"MXe1";"MX-Hotswap-1U";1;"K2_3";;;
77;"MXctrl1";"MX-Hotswap-1.25U";1;"K5_0";;;
78;"F1";"MX-Hotswap-1U";1;"K0_1";;;
79;"MXf2";"MX-Hotswap-1U";1;"K3_4";;;
80;"MXm1";"MX-Hotswap-1U";1;"K4_7";;;
81;"MX]1";"MX-Hotswap-1U";1;"K2_12";;;
82;"MXenter1";"MX-Hotswap-2.25U-ReversedStabilizers";1;"K3_12";;;
83;"MX+1";"MX-Hotswap-1U";1;"K1_12";;;
84;"MX9";"MX-Hotswap-1U";1;"K1_9";;;
85;"MXtab1";"MX-Hotswap-1.5U";1;"K2_0";;;
86;"MXy1";"MX-Hotswap-1U";1;"K2_6";;;
87;"MX8";"MX-Hotswap-1U";1;"K1_8";;;
88;"MXcaps1";"MX-Hotswap-1.75U";1;"K3_0";;;
89;"Y1";"Crystal_SMD_3225-4Pin_3.2x2.5mm";1;"16Mhz";;;
90;"MXp1";"MX-Hotswap-1U";1;"K2_10";;;
91;"MXo1";"MX-Hotswap-1U";1;"K2_9";;;
92;"F13";"MX-Hotswap-1U";1;"K0_13";;;
93;"MXc1";"MX-Hotswap-1U";1;"K4_3";;;
94;"MX6";"MX-Hotswap-1U";1;"K1_6";;;
95;"MX7";"MX-Hotswap-1U";1;"K1_7";;;
96;"MXsuper1";"MX-Hotswap-1.25U";1;"K5_1";;;
97;"ESC1";"MX-Hotswap-1U";1;"K0_0";;;

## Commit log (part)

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2026-04-04 Import MCU, host USB from ursaminor
    - Add LED and encoder nets
    - Make switch matrix the correct size.
2026-04-04 Add first draft of LED matrix
    Need to figure out if each LED needs a 100uf capacitor, and if the data
    line needs a resistor still. The datasheet is really hard to read
    because of low quality scan.
2026-04-10 Update schematic
    - Label all the keys to make sure I have them all
    - Reroute a few keys so that routing will be easier
    - Wire up the switch on the encoder
2026-04-11 Assign footprints
2026-04-11 Add board outline drawing
2026-04-12 Remove dangling trace
2026-04-15 Add Keebio-Parts library
    https://github.com/keebio/Keebio-Parts.pretty
2026-04-15 Add board outline to PCB design
2026-04-15 Move kicad library
2026-04-15 Update footprints
2026-04-16 Add Mx hotswap library
2026-04-16 Update schematic
    - fix avr isp pin out
    - add footprints to switches and leds
2026-04-18 Add another footprint library for switches and hotswaps
2026-04-18 Don't need that library
2026-04-18 Cleanup rotary encoder wiring
    - forgot a diode
    - don't need as many resistors. I looked at a couple other keyboards
    with rotary encoders and none of them had two sets of resistors.
2026-04-18 Fix footprint
2026-04-18 Add Mx_Alps_Hybrid library to get schematic symbols back
2026-04-18 Reorganize
2026-04-19 Get ERC to pass
2026-04-30 Start placing components on the pcb
2026-05-01 Place more footprints.
    Now I have to do a lot of measuring and get all the keyswitch locations
    dialed in.
2026-05-02 Rough place more componentso
    - Keys are mostly in the right place. I need to confirm the size of
    a few caps and then do fine measurements.
    - Placing the ribbon LEDs in a snake pattern. This will make routing
    easier but could complicate the firmware mapping.
2026-05-02 Place more footprints
2026-05-03 Rough placement of all the diodes
2026-05-03 All components roughly placed
2026-05-06 Dial in positions of a few keys and change the footprint of the usb connection.
    I need to find out what the keyboard's daughter card has on it, as this
    could be simpler to build.
2026-05-07 More incremental progress.
2026-05-09 Align row 5
2026-05-09 Fix up
2026-05-09 Get row 4 placed.
    Had to change the size of several switches as they were wrong.
2026-05-09 Place row 3
2026-05-10 Place row2
2026-05-10 Place row 1
    Fix \ footprint as it looks like 1.5u is the right size. I have to
    remeasure to be sure.
2026-05-11 Tune more of the switch footprints
2026-05-11 Simpler USB connection
    The keyboard case comes with a USBC breakout card. This card contains
    the 5.1K resistors, and what looks like an ESD on them. I've removed
    those from the schematics, and assigned a picoblade connector, as that
    is what I think the board is currently using.
2026-05-13 Get all components roughly placed
2026-05-14 Get the last footprints roughed in.
2026-05-14 Fix silkscreen
2026-05-18 Fix a bunch of alignment issues.
2026-05-18 Update footprints and adjust positioning
    I printed out the schematic and compare with the physical board and
    needed to make some adjustments.
2026-05-18 Move measures to user comments and start traces
2026-05-20 Fix a big schematic mistake
    I had two col5 nets! I only noticed this as I started routing the
    columns. I also fixed the numbering of all the switches.
2026-05-20 Route more columns
    The cpu area needs to be reworked once all the columns are roughed in.
2026-05-23 Add more traces
2026-05-24 Diode wiring is done
2026-05-24 Route a few LEDs
    Get a few complete keys together to better understand how the layout
    will work.
2026-05-24 Move diodes up so that wiring LEDs is and diodes is easier.
2026-05-25 Route part of row 1
    This was so much easier. I need to replace all the LEDS on Rows 0, 2, 4
    as the LEDS are much simpler to route going left to right. I'll have go
    figure out the signal loop back at the end of each row.
2026-05-28 Reposition all the LEDs so that routing isn't unhinged
2026-05-28 Position the LEDS more tightly
2026-05-28 Route the LEDs and make progress on the switch matrix
2026-05-30 route another row
2026-05-30 Route more keyswitches
2026-05-30 More routing progress
2026-05-30 More LED routing
2026-05-30 More routing
2026-05-30 Route 5v from connector to cpu
2026-06-01 Route more of 5V lines
2026-06-03 Add led switch backs.
    hopefully the distance doesn't matter too much
2026-06-05 Start connecting up the mcu
    reassign a bunch of pins to make routing easier.
2026-06-06 Route col 12 and 13
2026-06-06 route more of the switch matrix
2026-06-07 Rough routing is complete
    Still lots of small tweaks and clean up to do.
2026-06-07 Clean up routes
2026-06-07 Add ground plane fills and vias
2026-06-08 More vias for ground planes
2026-06-08 Clean up routing more
2026-06-09 Run cleanup and start resovling DRC errors.
2026-06-10 Fix a pile of DRC errors
    Still quite a few to go sadly
2026-06-10 Got DRC passing.
    - Improved back silkscreen to make it easier to assemble as a novice.
2026-06-10 Add screenshots
2026-06-13 Tweak routing
2026-06-14 Tested in paper again with switch plate.
    Need to adjust a few holes. Still have to move the rotary encoder.
2026-06-14 Adjust position of holes and encoder
    After a paper test these elements needed repositioning
2026-06-23 Generate firmware prototype with qmk new-keyboard
2026-06-24 Get board to build.
    qmk compile -kb sentryencoder -km default
2026-06-24 Closer to firmware that might work
    - Get pins updated
    - Cleanup matrix to align with schematic
    - I've completely hosed the visual layout. I need to fix this.
2026-06-27 Update visual layout
2026-06-27 Tweak layout more
2026-06-28 Get firmware compiling and make first pass at visual layout
2026-06-28 Revert "Get firmware compiling and make first pass at visual layout"
    This reverts commit 5ebebc94c5844c5c29fdd73ee73f03f4d7382e5b.
2026-06-28 Fix ordering of home/end
2026-06-28 Update pins for encoder
    I had the encoder and a switch on the same row/col
2026-06-28 Routing tweaks
2026-06-28 Update keymap and visual layout.
    qmk info can show you the visual representation for your keys and led
    matrix.
2026-06-30 Update keymap and wire up encoder to volume
2026-06-30 Make progress on defining the LED matrix
